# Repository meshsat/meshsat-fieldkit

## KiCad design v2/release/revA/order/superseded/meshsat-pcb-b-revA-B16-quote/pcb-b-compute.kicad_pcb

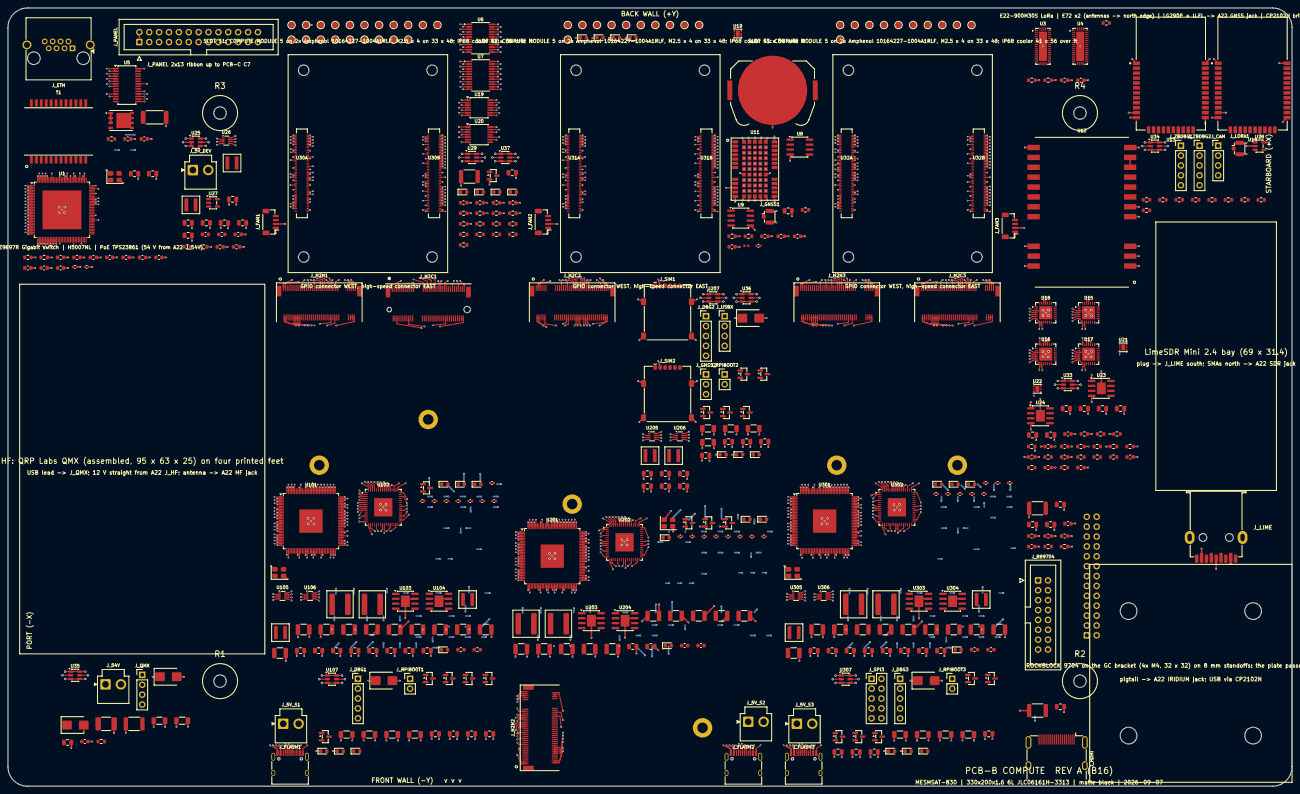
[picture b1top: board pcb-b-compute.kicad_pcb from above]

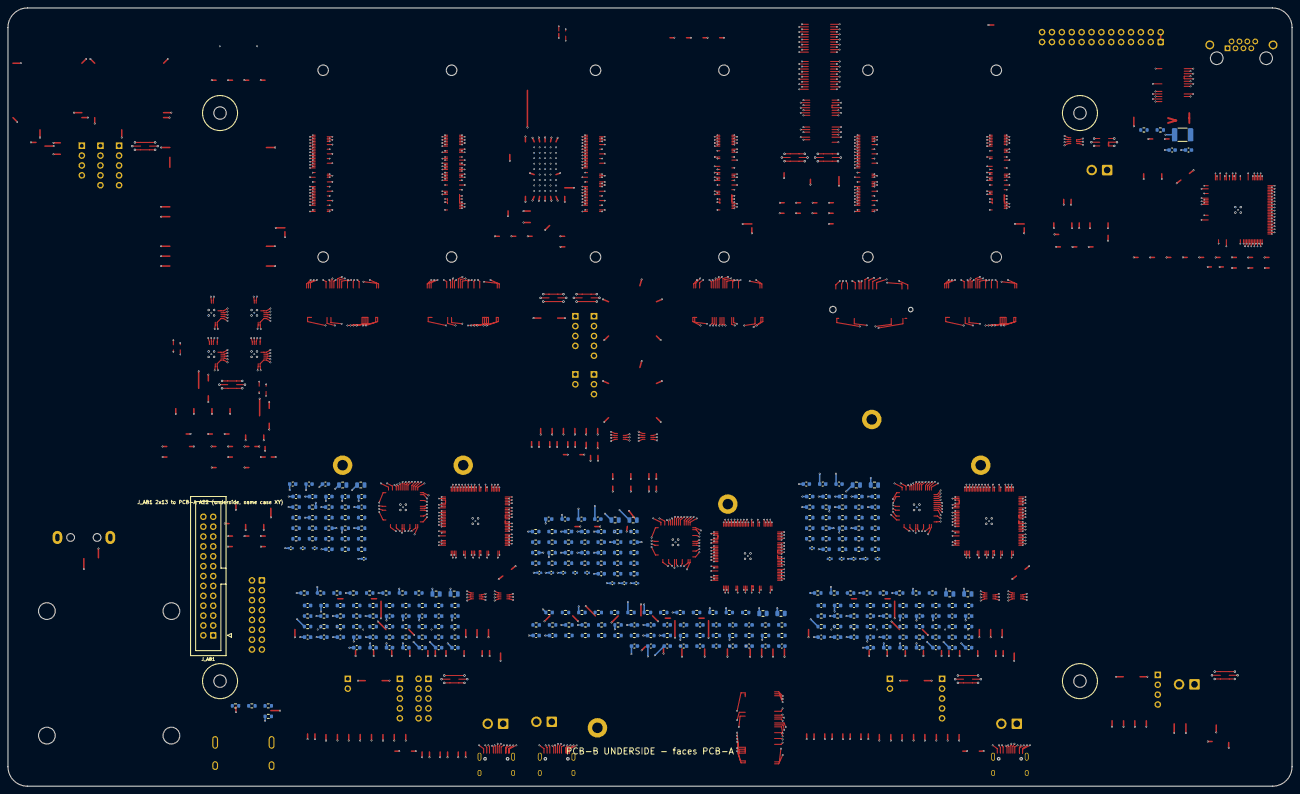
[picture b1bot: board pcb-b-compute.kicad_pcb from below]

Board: 6 copper layers, 330.0 x 200.0 mm, 777 parts (303 on the bottom side), 682 nets.

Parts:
BT1: CR2032 holder Keystone 3034: VBAT for the three m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; BatteryHolder_Keystone_3034_1x20mm
C1, C2, C101, C102, C103, C104, C201, C202, C203, C204, C301, C302, C303, C304: 100u 10V; C_1206_3216Metric
C3, C10, C17, C18, C19, C20, C21, C22, C23, C24, C25, C26, C29, C30, C31, C32, C36, C37, C38, C40, C44, C47, C49, C51, C54, C55, C57, C60, C62, C65, C66, C67, C68, C69, C70, C71, C110, C111, C118, C128, C133, C135, C136, C137, C138, C139, C140, C141, C142, C143, C144, C145, C146, C150, C158, C166, C167, C168, C169, C170, C171, C172, C173, C210, C211, C218, C228, C233, C235, C236, C237, C238, C239, C240, C241, C242, C243, C244, C245, C246, C250, C258, C266, C267, C268, C269, C270, C271, C272, C273, C286, C289, C310, C311, C318, C328, C333, C335, C336, C337, C338, C339, C340, C341, C342, C343, C344, C345, C346, C350, C358, C366, C367, C368, C369, C370, C371, C372, C373: 100n; C_0603_1608Metric
C4, C7, C16, C27, C28, C39, C41, C46, C53, C64, C105, C106, C107, C108, C109, C125, C130, C147, C148, C174, C205, C206, C207, C208, C209, C225, C230, C247, C248, C274, C305, C306, C307, C308, C309, C325, C330, C347, C348, C374: 10u; C_0805_2012Metric
C5, C6, C8, C9, C58, C63, C126, C127, C131, C132, C149, C157, C226, C227, C231, C232, C249, C257, C326, C327, C331, C332, C349, C357: 22u 6.3V; C_0805_2012Metric
C11, C56, C61, C129, C134, C229, C234, C329, C334: 10n; C_0603_1608Metric
C12, C13, C163, C263, C363: 1u; C_0603_1608Metric
C14, C15, C164, C165, C264, C265, C364, C365: 18p; C_0402_1005Metric
C33: 1n 2kV; C_1812_4532Metric
C34: 100n 100V; C_0805_2012Metric
C35: 10u 100V; C_1812_4532Metric
C42: 47p; C_0402_1005Metric
C43, C48, C50, C59: 4.7u; C_0805_2012Metric
C45, C52: 1n; C_0603_1608Metric
C112, C113, C114, C115, C116, C119, C120, C121, C122, C123, C212, C213, C214, C215, C216, C219, C220, C221, C222, C223, C312, C313, C314, C315, C316, C319, C320, C321, C322, C323: 22u 10V X7R 1210; C_1210_3225Metric
C117, C124, C217, C224, C317, C324: 3.3n; C_0603_1608Metric
C159, C160, C161, C162, C175, C176, C177, C178, C179, C180, C181, C182, C259, C260, C275, C276, C277, C278, C279, C280, C281, C282, C359, C360, C375, C376, C377, C378, C379, C380, C381, C382: 100n; C_0402_1005Metric
C287, C288, C290, C291: 33p; C_0402_1005Metric
D1, D101, D201, D301: SMBJ5.0A; D_SMB
D2: SMBJ58A; D_SMB
F1: 2A hold 1812; Fuse_1812_4532Metric
F2, F3, F4: 0.5A hold 1812; Fuse_1812_4532Metric
H1: M3 rod R1; MountingHole_3.2mm_M3
H2: M3 rod R2; MountingHole_3.2mm_M3
H3: M3 rod R3; MountingHole_3.2mm_M3
H4: M3 rod R4; MountingHole_3.2mm_M3
H5, H6, H7, H8: M2.5 standoff 4.0 mm, CM5 slot S1; MountingHole_2.7mm_M2.5
H9, H10, H11, H12: M2.5 standoff 4.0 mm, CM5 slot S2; MountingHole_2.7mm_M2.5
H13, H14, H15, H16: M2.5 standoff 4.0 mm, CM5 slot S3; MountingHole_2.7mm_M2.5
H17, H18, H19, H20: M4, GC 9704 bracket; MountingHole_4.3mm_M4
J_5V_DEV: USB device rail from A22 J_5V_DEV (JST-VH): + -; JST_VH_B2P-VH_1x02_P3.96mm_Vertical
J_5V_S1: 5 V slot rail S1 from A22 J_5V_S1 (JST-VH, 16 AWG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; JST_VH_B2P-VH_1x02_P3.96mm_Vertical
J_5V_S2: 5 V slot rail S2 from A22 J_5V_S2 (JST-VH, 16 AWG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; JST_VH_B2P-VH_1x02_P3.96mm_Vertical
J_5V_S3: 5 V slot rail S3 from A22 J_5V_S3 (JST-VH, 16 AWG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; JST_VH_B2P-VH_1x02_P3.96mm_Vertical
J_54V: 54 V PoE feed from A22 J_54V (JST-VH): + -; JST_VH_B2P-VH_1x02_P3.96mm_Vertical
J_AB1: A-B interconnect (IDC 2x13, underside, mates A22'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; IDC-Header_2x13_P2.54mm_Vertical
J_CAM: camera lead (USB 2.0, S1 hub port 3): 5V D- D+ GND; PinHeader_1x04_P2.54mm_Vertical
J_DBG1: console UART0 and the module I2C of S1 (3.3 V, be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; PinHeader_1x05_P2.54mm_Vertical
J_DBG2: console UART0 and the module I2C of S2 (3.3 V, be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; PinHeader_1x05_P2.54mm_Vertical
J_DBG3: console UART0 and the module I2C of S3 (3.3 V, be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; PinHeader_1x05_P2.54mm_Vertical
J_ETH: RJ45 jack (Amphenol RJHSE5380): patch lead to the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; RJ45_Amphenol_RJHSE5380
J_FAN1: IP68 cooler fan of S1 (JST-SH 1.0): 5V GND TACHO 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; JST_SH_BM04B-SRSS-TB_1x04-1MP_P1.00mm_Vertical
J_FAN2: IP68 cooler fan of S2 (JST-SH 1.0): 5V GND TACHO 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; JST_SH_BM04B-SRSS-TB_1x04-1MP_P1.00mm_Vertical
J_FAN3: IP68 cooler fan of S3 (JST-SH 1.0): 5V GND TACHO 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; JST_SH_BM04B-SRSS-TB_1x04-1MP_P1.00mm_Vertical
J_FLASH1, J_FLASH2, J_FLASH3: USB-C 2.0 receptacle; USB_C_Receptacle_HRO_TYPE-C-31-M-12
J_GNSS1: U.FL: pigtail to A22's GNSS jack J_RF4; U.FL_Hirose_U.FL-R-SMT-1_Vertical
J_GNSS2: LG290P UART2 (bench): GND TX RX; PinHeader_1x03_P2.54mm_Vertical
J_HDMI: HDMI type A receptacle (Molex 208658-1001): cable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; HDMI_A_Molex_208658-1001_Horizontal
J_LIME: USB 3.0 type A receptacle (Wuerth 692122030100 la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; USB3_A_Receptacle_Wuerth_692122030100
J_LORA1: U.FL: pigtail to A22's LoRa jack J_RF11; U.FL_Hirose_U.FL-R-SMT-1_Vertical
J_M2C1: M.2 E-key 2230 socket, TE 2199230-4, M2.5 standof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; M2_E-Key_Socket_2230
J_M2C2: M.2 B-key 3052 socket, TE 1-2199119-5, M2.5 stand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; M2_B-Key_Socket_3052
J_M2C3, J_M2N1, J_M2N2, J_M2N3: M.2 M-key 2242 socket, Amphenol MDT420M02001, M2.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; M2_M-Key_Socket_2242
J_PANEL: panel ribbon to PCB-C C7 (IDC 2x13): the RP2040 p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; IDC-Header_2x13_P2.54mm_Vertical
J_QMX: QMX USB lead (S2 hub port 4): VBUS D- D+ GND; pig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; PinHeader_1x04_P2.54mm_Vertical
J_RB9704: RockBLOCK 9704 16-pin (IDC 2x8) on the Ground Con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; IDC-Header_2x08_P2.54mm_Vertical
J_RPIBOOT1: nRPIBOOT jumper S1: fit to flash the eMMC over J_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; PinHeader_1x02_P2.54mm_Vertical
J_RPIBOOT2: nRPIBOOT jumper S2: fit to flash the eMMC over J_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; PinHeader_1x02_P2.54mm_Vertical
J_RPIBOOT3: nRPIBOOT jumper S3: fit to flash the eMMC over J_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; PinHeader_1x02_P2.54mm_Vertical
J_SIM1: nano-SIM push-push GCT SIM8060 (SIM 1); nanoSIM_GCT_SIM8060-6-0-14-00
J_SIM2: nano-SIM push-push GCT SIM8060 (SIM 2); nanoSIM_GCT_SIM8060-6-0-14-00
J_SPI3: SPI0 breakout of S3 (2x5): 3V3 GND MISO MOSI SCLK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; PinHeader_2x05_P2.54mm_Vertical
J_USBX: spare USB 2.0 header (S3 hub port 4): 5V D- D+ GND; PinHeader_1x04_P2.54mm_Vertical
J_ZBDBG1: CC2652P cJTAG ZBA (bench): 3V3 GND TMSC TCKC RESET; PinHeader_1x05_P2.54mm_Vertical
J_ZBDBG2: CC2652P cJTAG ZBB (bench): 3V3 GND TMSC TCKC RESET; PinHeader_1x05_P2.54mm_Vertical
L1: 4.7uH XAL4020-472ME; L_Coilcraft_XAL4020-XXX
L2, L103, L104, L203, L204, L303, L304: 2.2uH XAL4020-222ME; L_Coilcraft_XAL4020-XXX
L3: 27nH 0402 (antenna bias tee); L_0402_1005Metric
L101, L102, L201, L202, L301, L302: 3.3uH XAL6060-332ME; L_Coilcraft_XAL6060-XXX
LED1: green Ethernet port 1 link; LED_0603_1608Metric
LED2: green Ethernet port 2 link; LED_0603_1608Metric
LED3: green Ethernet port 3 link; LED_0603_1608Metric
LED4: green Ethernet port 4 link; LED_0603_1608Metric
LED6: red ZBA (DIO_7); LED_0603_1608Metric
LED7: green ZBA (DIO_8); LED_0603_1608Metric
LED8: red ZBB (DIO_7); LED_0603_1608Metric
LED9: green ZBB (DIO_8); LED_0603_1608Metric
LED11: green 5 V S1; LED_0603_1608Metric
LED12, LED22, LED32: green NVMe link (PORTSTATUS0); LED_0603_1608Metric
LED13, LED23, LED33: green card link (PORTSTATUS1); LED_0603_1608Metric
LED14, LED24, LED34: amber NVMe activity; LED_0603_1608Metric
LED15: blue WiFi link; LED_0603_1608Metric
LED16, LED26, LED36: green ACT (LED_nACT sinks); LED_0603_1608Metric
LED17, LED27, LED37: red PWR; LED_0603_1608Metric
LED21: green 5 V S2; LED_0603_1608Metric
LED25: amber 5G network; LED_0603_1608Metric
LED31: green 5 V S3; LED_0603_1608Metric
LED35: amber spare drive activity; LED_0603_1608Metric
Q1: FDMC3612 100 V N-FET, PoE port switch (PowerPAK S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; PowerPAK_SO-8_Single
Q2: 2N7002 expander -> switch reset; SOT-23
Q101, Q201, Q301: BC857: LED_nPWR must be buffered (datasheet Table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; SOT-23
Q102, Q103, Q104, Q105, Q202, Q203, Q204, Q205, Q302, Q303, Q304, Q305: 2N7002; SOT-23
Q106, Q206: 2N7002 EMCON -> W_DISABLE1#; SOT-23
Q207: 2N7002 expander -> FULL_CARD_POWER_OFF#; SOT-23
Q208: 2N7002 expander -> RESET#; SOT-23
R1, R103, R108, R113, R115, R144, R203, R208, R213, R215, R244, R303, R308, R313, R315, R344: 10k 1%; R_0603_1608Metric
R2: 20.0k 1%; R_0603_1608Metric
R3: 6.04k 1% (ISET); R_0603_1608Metric
R4, R11, R14, R21, R22, R25, R28, R29, R30, R31, R37, R41, R42, R44, R47, R56, R132, R133, R134, R135, R137, R138, R141, R145, R146, R149, R151, R154, R155, R156, R157, R158, R232, R233, R234, R235, R237, R238, R240, R241, R245, R246, R249, R251, R254, R255, R256, R257, R258, R332, R333, R334, R335, R337, R341, R345, R346, R349, R351, R354, R355, R356, R357, R358: 10k; R_0603_1608Metric
R5, R6, R7, R8, R24, R26, R27, R32, R33, R34, R35, R40, R101, R129, R130, R131, R136, R139, R148, R150, R201, R229, R230, R231, R236, R239, R248, R250, R301, R329, R330, R331, R336, R339, R348, R350: 1k; R_0603_1608Metric
R9, R10: 75; R_0603_1608Metric
R12: 0.255R 1% 2512; R_2512_6332Metric
R13: 24.9 (POE_P tie); R_0603_1608Metric
R15, R16, R48, R49, R50, R51, R52, R53, R106, R111, R112, R206, R211, R212, R306, R311, R312: 100k; R_0603_1608Metric
R17, R18, R54, R55: 2.2k; R_0603_1608Metric
R19: 15k; R_0603_1608Metric
R20, R105, R110, R205, R210, R305, R310: 22k; R_0603_1608Metric
R23: 10R; R_0603_1608Metric
R36, R43: 3.0 A (ILM); R_0603_1608Metric
R38, R45: 100k 1%; R_0603_1608Metric
R39, R46: 10k 1% (OVLO); R_0603_1608Metric
R57: 1k (strap [LED4_1, LED3_1] = 01: I2C management, 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; R_0603_1608Metric
R102, R107, R202, R207, R302, R307: 31.6k 1%; R_0603_1608Metric
R104, R109, R204, R209, R304, R309: 68k (RT: 500 kHz); R_0603_1608Metric
R114, R214, R314: 40.2k 1%; R_0603_1608Metric
R116, R216, R316: 26.7k 1%; R_0603_1608Metric
R117, R217, R317: 475 1% (IREF); R_0603_1608Metric
R118, R218, R318: 1.43k 1% (REXT); R_0603_1608Metric
R119, R120, R121, R123, R125, R126, R152, R153, R219, R220, R221, R223, R225, R226, R252, R253, R319, R320, R321, R323, R325, R326, R352, R353: 5.1k; R_0603_1608Metric
R122, R124, R128, R222, R224, R228, R322, R324, R328: 330; R_0603_1608Metric
R127, R227, R327: 4.7k; R_0603_1608Metric
R142, R242, R342: 9.53k 1%; R_0603_1608Metric
R143, R243, R343: 90.9k 1%; R_0603_1608Metric
R147, R247, R347: 1M; R_0603_1608Metric
S_LIME1, S_LIME2: tie slot; Slot_5x1.8_NPTH
S_QMX1, S_QMX2, S_QMX3, S_QMX4: tie slot; Slot_5x1.8_NPTH
T1: Pulse H5007NL 1000BASE-T magnetics (switch port 4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; Pulse_H5007NL
TP1: AB_SPARE; TestPoint_Pad_D1.5mm
TP2: +5V_DEV; TestPoint_Pad_D1.5mm
TP3: +3V3_DEV; TestPoint_Pad_D1.5mm
TP4: +1V2_KSZ; TestPoint_Pad_D1.5mm
TP5: +2V5_KSZ; TestPoint_Pad_D1.5mm
TP6: VBAT; TestPoint_Pad_D1.5mm
TP7: EMCON_HW; TestPoint_Pad_D1.5mm
TP8: ZEROIZE_HW; TestPoint_Pad_D1.5mm
TP9: GNSS_PPS; TestPoint_Pad_D1.5mm
TP10: SDA; TestPoint_Pad_D1.5mm
TP11: SCL; TestPoint_Pad_D1.5mm
TP12: +54V_POE; TestPoint_Pad_D1.5mm
TP13: POE_DRAIN; TestPoint_Pad_D1.5mm
TP14: +5V_LIME; TestPoint_Pad_D1.5mm
TP15: +5V_RB; TestPoint_Pad_D1.5mm
TP16: +5V_LORA; TestPoint_Pad_D1.5mm
TP17: +3V3_ZB; TestPoint_Pad_D1.5mm
TP18: HDMI_SEL1; TestPoint_Pad_D1.5mm
TP19: HDMI_SEL2; TestPoint_Pad_D1.5mm
TP20: +3V3_S1A; TestPoint_Pad_D1.5mm
TP21: +3V3_S1B; TestPoint_Pad_D1.5mm
TP22: +1V0_S1; TestPoint_Pad_D1.5mm
TP23: +1V1_S1; TestPoint_Pad_D1.5mm
TP24: +3V3_S2A; TestPoint_Pad_D1.5mm
TP25: +3V3_S2B; TestPoint_Pad_D1.5mm
TP26: +1V0_S2; TestPoint_Pad_D1.5mm
TP27: +1V1_S2; TestPoint_Pad_D1.5mm
TP28: +3V3_S3A; TestPoint_Pad_D1.5mm
TP29: +3V3_S3B; TestPoint_Pad_D1.5mm
TP30: +1V0_S3; TestPoint_Pad_D1.5mm
TP31: +1V1_S3; TestPoint_Pad_D1.5mm
TP41: EXP_SPARE1; TestPoint_Pad_D1.5mm
TP42: EXP_SPARE2; TestPoint_Pad_D1.5mm
TP43: EXP_SPARE3; TestPoint_Pad_D1.5mm
TP44: EXP_SPARE4; TestPoint_Pad_D1.5mm
TP45: EXP_SPARE5; TestPoint_Pad_D1.5mm
TP46: EXP_SPARE6; TestPoint_Pad_D1.5mm
TP47: EXP_SPARE7; TestPoint_Pad_D1.5mm
TP48: EXP_SPARE8; TestPoint_Pad_D1.5mm
TP49: EXP_SPARE9; TestPoint_Pad_D1.5mm
TP50: EXP_SPARE10; TestPoint_Pad_D1.5mm
TP51: EXP_SPARE11; TestPoint_Pad_D1.5mm
U1: Microchip KSZ9897RTXI seven-port Gigabit switch: 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; TQFP-128_14x14mm_P0.4mm_EP10.0
U3: TI TS3DV642A0RUAR HDMI 2:1 switch (HDMI1 / HDMI2 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; WQFN-42-1EP_3.5x9mm_P0.5mm_EP2.05x7.55mm
U4: TI TS3DV642A0RUAR HDMI 2:1 switch (HDMIM / HDMI3 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; WQFN-42-1EP_3.5x9mm_P0.5mm_EP2.05x7.55mm
U5: TI TPS23861PWR PoE PSE controller, port 1 to the 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; TSSOP-28_4.4x9.7mm_P0.65mm
U6: PCA9555PW 0x20: outputs (switch reset, rail enabl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; TSSOP-24_4.4x7.8mm_P0.65mm
U7: PCA9555PW 0x25: inputs (faults, RockBLOCK status)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; TSSOP-24_4.4x7.8mm_P0.65mm
U8: ATECC608B-SSHDA-T secure element (I2C 0x60): keys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; SOIC-8_3.9x4.9mm_P1.27mm
U9: DS3231MZ+ holdover clock (I2C 0x68), CR2032 backed; SOIC-8_3.9x4.9mm_P1.27mm
U10: TMP117AIDRVR board temperature under the coolers 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; WSON-6-1EP_2x2mm_P0.65mm_EP1x1.6mm
U11: Quectel LG290P03AAMD GNSS RTK module: UART1 to th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; Quectel_LG290P
U12: Ebyte E22-900M30S 1 W LoRa (SX1262) on S3 SPI0 CE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; Ebyte_E22-900M30S
U13: Ebyte E72-2G4M20S1E CC2652P (Zigbee coordinator):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; Ebyte_E72-2G4M20S1E
U14: Ebyte E72-2G4M20S1E CC2652P (OpenThread RCP for M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; Ebyte_E72-2G4M20S1E
U15: CP2102N-A02-GQFN28 USB-UART bridge (GNSS); QFN-28-1EP_5x5mm_P0.5mm_EP3.35x3.35mm
U16: CP2102N-A02-GQFN28 USB-UART bridge (ZBA); QFN-28-1EP_5x5mm_P0.5mm_EP3.35x3.35mm
U17: CP2102N-A02-GQFN28 USB-UART bridge (ZBB); QFN-28-1EP_5x5mm_P0.5mm_EP3.35x3.35mm
U18: CP2102N-A02-GQFN28 USB-UART bridge (RB); QFN-28-1EP_5x5mm_P0.5mm_EP3.35x3.35mm
U19: 74LVC08APW quad AND: LimeSDR (hub port power AND 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; TSSOP-14_4.4x5mm_P0.65mm
U20: 74LVC08APW quad AND: E72 radios (EMCON AND softwa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; TSSOP-14_4.4x5mm_P0.65mm
U21, U22: TPS22810DRV; WSON-6-1EP_2x2mm_P0.65mm_EP1x1.6mm
U23: TPS259631DDAR eFuse +5V_DEV -> +5V_LIME (3.0 A (I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; SOIC-8-1EP_3.9x4.9mm_P1.27mm_EP2.29x3mm
U24: TPS259631DDAR eFuse +5V_DEV -> +5V_RB (3.0 A (ILM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; SOIC-8-1EP_3.9x4.9mm_P1.27mm_EP2.29x3mm
U25: AP63203WU-7 3.3 V 2 A buck: the shared logic (+3V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; TSOT-23-6
U26: TPS62933DRLR buck 1.2 V Ethernet switch core; SOT-583-8
U27: AP2112K-2.5 LDO: the switch's 2.5 V analog rail; SOT-23-5
U28: TPS2065CDBV; SOT-23-5
U29, U33, U34, U35, U36, U37, U107, U207, U307: USBLC6-2SC6; SOT-23-6
U30A: Amphenol 10164227-1004A1RLF receptacle A, slot S1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; CM5_Conn_A_10164227
U30B: Amphenol 10164227-1004A1RLF receptacle B, slot S1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; CM5_Conn_B_10164227
U31A: Amphenol 10164227-1004A1RLF receptacle A, slot S2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; CM5_Conn_A_10164227
U31B: Amphenol 10164227-1004A1RLF receptacle B, slot S2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; CM5_Conn_B_10164227
U32A: Amphenol 10164227-1004A1RLF receptacle A, slot S3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; CM5_Conn_A_10164227
U32B: Amphenol 10164227-1004A1RLF receptacle B, slot S3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; CM5_Conn_B_10164227
U101: Diodes PI7C9X2G404SL PCIe 2.0 switch, slot S1: up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; LQFP-128_14x14mm_P0.4mm_EP6.0
U102: TI TUSB8041IRGCR four-port USB 3.0 hub, slot S1 (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; QFN-64-1EP_9x9mm_P0.5mm_EP4.7x4.7mm
U103: AP64500SP-13 5 A buck, 3.3 V rail +3V3_S1A; SOIC-8-1EP_3.9x4.9mm_P1.27mm_EP2.29x3mm
U104: AP64500SP-13 5 A buck, 3.3 V rail +3V3_S1B; SOIC-8-1EP_3.9x4.9mm_P1.27mm_EP2.29x3mm
U105: TPS62933DRLR buck 1.0 V PCIe switch core S1; SOT-583-8
U106: TPS62933DRLR buck 1.1 V hub core S1; SOT-583-8
U201: Diodes PI7C9X2G404SL PCIe 2.0 switch, slot S2: up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; LQFP-128_14x14mm_P0.4mm_EP6.0
U202: TI TUSB8041IRGCR four-port USB 3.0 hub, slot S2 (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; QFN-64-1EP_9x9mm_P0.5mm_EP4.7x4.7mm
U203: AP64500SP-13 5 A buck, 3.3 V rail +3V3_S2A; SOIC-8-1EP_3.9x4.9mm_P1.27mm_EP2.29x3mm
U204: AP64500SP-13 5 A buck, 3.3 V rail +3V3_S2B; SOIC-8-1EP_3.9x4.9mm_P1.27mm_EP2.29x3mm
U205: TPS62933DRLR buck 1.0 V PCIe switch core S2; SOT-583-8
U206: TPS62933DRLR buck 1.1 V hub core S2; SOT-583-8
U301: Diodes PI7C9X2G404SL PCIe 2.0 switch, slot S3: up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; LQFP-128_14x14mm_P0.4mm_EP6.0
U302: TI TUSB8041IRGCR four-port USB 3.0 hub, slot S3 (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; QFN-64-1EP_9x9mm_P0.5mm_EP4.7x4.7mm
U303: AP64500SP-13 5 A buck, 3.3 V rail +3V3_S3A; SOIC-8-1EP_3.9x4.9mm_P1.27mm_EP2.29x3mm
U304: AP64500SP-13 5 A buck, 3.3 V rail +3V3_S3B; SOIC-8-1EP_3.9x4.9mm_P1.27mm_EP2.29x3mm
U305: TPS62933DRLR buck 1.0 V PCIe switch core S3; SOT-583-8
U306: TPS62933DRLR buck 1.1 V hub core S3; SOT-583-8
Y1: 25 MHz 3225; Crystal_SMD_3225-4Pin_3.2x2.5mm
Y101, Y201, Y301: 24 MHz 3225; Crystal_SMD_3225-4Pin_3.2x2.5mm

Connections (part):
/5G_OFF: Q207.1, U6.10
/5G_PWROFF_n: J_M2C2.6, Q207.3, R238.1
/5G_RESET: Q208.1, U6.11
/5G_RST_n: J_M2C2.67, Q208.3, R240.1
/5G_W_DIS_n: J_M2C2.8, Q206.2, R237.1
/5G_nLED: J_M2C2.10, LED25.1
/+1V0_S1: C126.1, C127.1, C141.1, C142.1, C143.1, C144.1, C145.1, C146.1, C148.1, L103.2, R113.1, TP22.1, U101.3, U101.13, U101.14, U101.23, U101.29, U101.31, U101.40, U101.55, U101.62, U101.65, U101.91, U101.99, U101.105, U101.108, U101.119, U101.125
/+1V0_S2: C226.1, C227.1, C241.1, C242.1, C243.1, C244.1, C245.1, C246.1, C248.1, L203.2, R213.1, TP26.1, U201.3, U201.13, U201.14, U201.23, U201.29, U201.31, U201.40, U201.55, U201.62, U201.65, U201.91, U201.99, U201.105, U201.108, U201.119, U201.125
/+1V0_S3: C326.1, C327.1, C341.1, C342.1, C343.1, C344.1, C345.1, C346.1, C348.1, L303.2, R313.1, TP30.1, U301.3, U301.13, U301.14, U301.23, U301.29, U301.31, U301.40, U301.55, U301.62, U301.65, U301.91, U301.99, U301.105, U301.108, U301.119, U301.125
/+1V1_S1: C131.1, C132.1, C166.1, C167.1, C168.1, C169.1, C174.1, L104.2, R115.1, TP23.1, U102.5, U102.8, U102.13, U102.21, U102.28, U102.31, U102.51, U102.57
/+1V1_S2: C231.1, C232.1, C266.1, C267.1, C268.1, C269.1, C274.1, L204.2, R215.1, TP27.1, U202.5, U202.8, U202.13, U202.21, U202.28, U202.31, U202.51, U202.57
/+1V1_S3: C331.1, C332.1, C366.1, C367.1, C368.1, C369.1, C374.1, L304.2, R315.1, TP31.1, U302.5, U302.8, U302.13, U302.21, U302.28, U302.31, U302.51, U302.57
/+1V2_KSZ: C8.1, C9.1, C18.1, C21.1, C24.1, C27.1, L2.2, R1.1, TP4.1, U1.3, U1.11, U1.14, U1.19, U1.23, U1.30, U1.36, U1.41, U1.45, U1.56, U1.74, U1.87, U1.104, U1.110, U1.114, U1.119, U1.124
/+1V8_CM1: U30A.88, U30A.90
/+1V8_CM2: U31A.88, U31A.90
/+1V8_CM3: U32A.88, U32A.90
/+2V5_KSZ: C12.1, C19.1, C22.1, C25.1, C28.1, TP5.1, U1.10, U1.22, U1.33, U1.44, U1.111, U1.122, U1.128, U27.5
/+3V3_CM1: C109.1, C110.1, Q101.2, Q102.1, Q103.1, Q104.1, Q105.1, R111.1, R148.1, R151.2, R154.2, R155.2, R156.2, R157.2, U30A.78, U30A.84, U30A.86
/+3V3_CM2: C209.1, C210.1, Q201.2, Q202.1, Q203.1, Q204.1, Q205.1, R211.1, R248.1, R251.2, R254.2, R255.2, R256.2, R257.2, U31A.78, U31A.84, U31A.86
/+3V3_CM3: C309.1, C310.1, Q301.2, Q302.1, Q303.1, Q304.1, Q305.1, R311.1, R348.1, R351.2, R354.2, R355.2, R356.2, R357.2, U32A.78, U32A.84, U32A.86
/+3V3_DEV: C5.1, C6.1, C13.1, C17.1, C20.1, C23.1, C26.1, C36.1, C37.1, C38.1, C40.1, C41.1, C65.1, C66.1, C67.1, C68.1, C69.1, C70.1, C71.1, L1.2, R4.2, R5.1, R6.1, R7.1, R8.1, R11.2, R14.2, R21.2, R37.2, R41.2, R42.2, R44.2, R47.2, R54.2, R55.2, R56.2, R158.2, R258.2, R358.2, TP3.1, U1.61, U1.77, U1.99, U3.1, U4.1, U5.1, U6.24, U7.3, U7.21, U7.24, U8.8, U9.2, U10.4, U10.5, U11.23, U19.14, U20.14, U22.6, U25.1, U27.1, U27.3, U29.5, U37.5
/+3V3_S1A: C114.1, C115.1, C116.1, C157.1, C158.1, J_M2C1.2, J_M2C1.4, J_M2C1.72, J_M2C1.74, L101.2, Q106.1, R102.1, R134.2, R137.2, R138.2, R139.1, TP20.1
/+3V3_S1B: C121.1, C122.1, C123.1, C135.1, C136.1, C137.1, C138.1, C139.1, C140.1, C147.1, C149.1, C150.1, C170.1, C171.1, C172.1, C173.1, J_M2N1.2, J_M2N1.4, J_M2N1.12, J_M2N1.14, J_M2N1.16, J_M2N1.18, J_M2N1.70, J_M2N1.72, J_M2N1.74, L102.2, R107.1, R119.2, R120.2, R121.2, R123.2, R125.2, R126.2, R130.1, R131.1, R132.2, R133.2, R136.1, R141.2, R145.2, R146.2, TP21.1, U101.1, U101.8, U101.15, U101.49, U101.64, U101.79, U101.82, U101.84, U101.96, U101.113, U102.16, U102.34, U102.52, U102.63
/+3V3_S2A: C214.1, C215.1, C216.1, C257.1, C258.1, J_M2C2.2, J_M2C2.4, J_M2C2.70, J_M2C2.72, J_M2C2.74, L201.2, Q206.1, R202.1, R234.2, R237.2, R238.2, R239.1, R240.2, TP24.1
/+3V3_S2B: C221.1, C222.1, C223.1, C235.1, C236.1, C237.1, C238.1, C239.1, C240.1, C247.1, C249.1, C250.1, C270.1, C271.1, C272.1, C273.1, J_M2N2.2, J_M2N2.4, J_M2N2.12, J_M2N2.14, J_M2N2.16, J_M2N2.18, J_M2N2.70, J_M2N2.72, J_M2N2.74, L202.2, R207.1, R219.2, R220.2, R221.2, R223.2, R225.2, R226.2, R230.1, R231.1, R232.2, R233.2, R236.1, R241.2, R245.2, R246.2, TP25.1, U201.1, U201.8, U201.15, U201.49, U201.64, U201.79, U201.82, U201.84, U201.96, U201.113, U202.16, U202.34, U202.52, U202.63
/+3V3_S3A: C314.1, C315.1, C316.1, C357.1, C358.1, J_M2C3.2, J_M2C3.4, J_M2C3.12, J_M2C3.14, J_M2C3.16, J_M2C3.18, J_M2C3.70, J_M2C3.72, J_M2C3.74, L301.2, R302.1, R334.2, R339.1, TP28.1
/+3V3_S3B: C321.1, C322.1, C323.1, C335.1, C336.1, C337.1, C338.1, C339.1, C340.1, C347.1, C349.1, C350.1, C370.1, C371.1, C372.1, C373.1, J_M2N3.2, J_M2N3.4, J_M2N3.12, J_M2N3.14, J_M2N3.16, J_M2N3.18, J_M2N3.70, J_M2N3.72, J_M2N3.74, J_SPI3.1, L302.2, R25.2, R307.1, R319.2, R320.2, R321.2, R323.2, R325.2, R326.2, R330.1, R331.1, R332.2, R333.2, R336.1, R341.2, R345.2, R346.2, TP29.1, U301.1, U301.8, U301.15, U301.49, U301.64, U301.79, U301.82, U301.84, U301.96, U301.113, U302.16, U302.34, U302.52, U302.63
/+3V3_ZB: C53.1, C54.1, C55.1, J_ZBDBG1.1, J_ZBDBG2.1, R28.2, R29.2, R30.2, R31.2, TP17.1, U13.20, U14.20, U22.1
/+5V_CAM: C64.1, J_CAM.1, U28.1, U34.5
/+5V_DEV: C1.1, C2.1, C4.1, C7.1, C57.1, C62.1, D1.1, F1.1, F2.1, F3.1, F4.1, J_5V_DEV.1, R38.1, R45.1, TP2.1, U21.6, U23.4, U24.4, U25.2, U25.3, U26.2, U26.3, U28.5
/+5V_HDMI: C39.1, F2.2, J_HDMI.18, R17.2, R18.2
/+5V_LIME: C58.1, J_LIME.1, TP14.1, U23.5, U33.5
/+5V_LORA: C46.1, C47.1, TP16.1, U12.9, U12.10, U21.1
/+5V_RB: C63.1, J_RB9704.15, TP15.1, U24.5
/+5V_S1: C101.1, C102.1, C103.1, C104.1, C105.1, C106.1, C107.1, C108.1, C112.1, C113.1, C119.1, C120.1, C125.1, C130.1, D101.1, J_5V_S1.1, J_FAN1.1, R101.1, R143.1, U18.7, U18.8, U30A.77, U30A.79, U30A.81, U30A.83, U30A.85, U30A.87, U103.2, U104.2, U105.3, U106.3
/+5V_S2: C201.1, C202.1, C203.1, C204.1, C205.1, C206.1, C207.1, C208.1, C212.1, C213.1, C219.1, C220.1, C225.1, C230.1, D201.1, J_5V_S2.1, J_FAN2.1, R201.1, R243.1, U15.7, U15.8, U16.7, U16.8, U17.7, U17.8, U31A.77, U31A.79, U31A.81, U31A.83, U31A.85, U31A.87, U203.2, U204.2, U205.3, U206.3
/+5V_S3: C301.1, C302.1, C303.1, C304.1, C305.1, C306.1, C307.1, C308.1, C312.1, C313.1, C319.1, C320.1, C325.1, C330.1, D301.1, J_5V_S3.1, J_FAN3.1, R301.1, R343.1, U32A.77, U32A.79, U32A.81, U32A.83, U32A.85, U32A.87, U303.2, U304.2, U305.3, U306.3
/+5V_USBX: F4.2, J_USBX.1, U36.5
/+54V_POE: C34.1, C35.1, D2.1, J_54V.1, R13.1, TP12.1, U5.28
/AB_SPARE: J_AB1.25, TP1.1
/BOB: C33.1, R9.2, R10.2
/BT_nDIS1: U6.16, U30A.91
/BT_nDIS2: U6.17, U31A.91
/BT_nDIS3: U6.18, U32A.91
/CAM_DM: J_CAM.2, U34.3, U34.4, U102.18
/CAM_DP: J_CAM.3, U34.1, U34.6, U102.17
/CAM_EN: R48.1, U6.9, U28.4
/CAM_FLT: R47.1, U7.6, U28.3
/CARD1_CLKREQ_n: J_M2C1.53, R134.1
/CARD1_CLK_N: J_M2C1.49, U101.77
/CARD1_CLK_P: J_M2C1.47, U101.78
/CARD1_RX_N: J_M2C1.43, U101.107
/CARD1_RX_P: J_M2C1.41, U101.106
/CARD1_TX_N: J_M2C1.37, U101.103
/CARD1_TX_P: J_M2C1.35, U101.102
/CARD2_CLKREQ_n: J_M2C2.52, R234.1
/CARD2_CLK_N: J_M2C2.53, U201.77
/CARD2_CLK_P: J_M2C2.55, U201.78
/CARD2_RX_N: J_M2C2.41, U201.107
/CARD2_RX_P: J_M2C2.43, U201.106
/CARD2_TX_N: J_M2C2.47, U201.103
/CARD2_TX_P: J_M2C2.49, U201.102
/CARD3_CLKREQ_n: J_M2C3.52, R334.1
/CARD3_CLK_N: J_M2C3.53, U301.77
/CARD3_CLK_P: J_M2C3.55, U301.78
/CARD3_DEVSLP: J_M2C3.38, R337.1
/CARD3_RX_N: J_M2C3.41, U301.107
/CARD3_RX_P: J_M2C3.43, U301.106
/CARD3_TX_N: J_M2C3.47, U301.103
/CARD3_TX_P: J_M2C3.49, U301.102
/CARD3_nLED: J_M2C3.10, LED35.1
/CC1_F1: J_FLASH1.A5, R152.1
/CC1_F2: J_FLASH2.A5, R252.1
/CC1_F3: J_FLASH3.A5, R352.1
/CC2_F1: J_FLASH1.B5, R153.1
/CC2_F2: J_FLASH2.B5, R253.1
/CC2_F3: J_FLASH3.B5, R353.1
/DEV_BST: C3.1, U25.6
/DEV_SW: C3.2, L1.1, U25.5
/E22_CT: C45.1, U21.3
/E22_EN: U19.11, U21.5
/E72_CT: C52.1, U22.3
/E72_EN: U20.3, U22.5
/EMCON_HW: J_AB1.17, J_PANEL.8, Q106.3, Q206.3, TP7.1, U19.1, U19.9, U19.12, U20.1
/EN33_S1: R111.2, R112.1, U104.3, U105.2, U106.2
/EN33_S2: R211.2, R212.1, U204.3, U205.2, U206.2
/EN33_S3: R311.2, R312.1, U304.3, U305.2, U306.2
/ETH1_P0_N: C176.1, U30A.10
/ETH1_P0_P: C175.1, U30A.12
/ETH1_P1_N: C178.1, U30A.6
/ETH1_P1_P: C177.1, U30A.4
/ETH1_P2_N: C180.1, U30A.9
/ETH1_P2_P: C179.1, U30A.11
/ETH1_P3_N: C182.1, U30A.5
/ETH1_P3_P: C181.1, U30A.3
/ETH2_P0_N: C276.1, U31A.10
/ETH2_P0_P: C275.1, U31A.12
/ETH2_P1_N: C278.1, U31A.6
/ETH2_P1_P: C277.1, U31A.4
/ETH2_P2_N: C280.1, U31A.9
/ETH2_P2_P: C279.1, U31A.11
/ETH2_P3_N: C282.1, U31A.5
/ETH2_P3_P: C281.1, U31A.3
/ETH3_P0_N: C376.1, U32A.10
/ETH3_P0_P: C375.1, U32A.12
/ETH3_P1_N: C378.1, U32A.6
/ETH3_P1_P: C377.1, U32A.4
/ETH3_P2_N: C380.1, U32A.9
/ETH3_P2_P: C379.1, U32A.11
/ETH3_P3_N: C382.1, U32A.5
/ETH3_P3_P: C381.1, U32A.3
/EXP_INT: J_AB1.15, J_PANEL.6, R56.1, U1.94, U5.6, U6.1, U7.1, U9.3, U10.3
/EXP_SPARE1: TP41.1, U7.9
/EXP_SPARE2: TP42.1, U7.10
/EXP_SPARE3: TP43.1, U7.11
/EXP_SPARE4: TP44.1, U7.13
/EXP_SPARE5: TP45.1, U7.14
/EXP_SPARE6: TP46.1, U7.15
/EXP_SPARE7: TP47.1, U7.16
/EXP_SPARE8: TP48.1, U7.17
/EXP_SPARE9: TP49.1, U7.18
/EXP_SPARE10: TP50.1, U7.19
/EXP_SPARE11: TP51.1, U7.20
/FAN_PWM1: J_FAN1.4, R151.1, U30A.19
/FAN_PWM2: J_FAN2.4, R251.1, U31A.19
/FAN_PWM3: J_FAN3.4, R351.1, U32A.19
/FAN_TACHO1: J_FAN1.3, U30A.16
/FAN_TACHO2: J_FAN2.3, U31A.16
/FAN_TACHO3: J_FAN3.3, U32A.16
/GNSS_3V3: C43.1, C44.1, R24.2, U15.6
/GNSS_ANT: C42.1, J_GNSS1.1, L3.2
/GNSS_BIAS: L3.1, R23.2
/GNSS_DM: U15.5, U202.2
/GNSS_DP: U15.4, U202.1
/GNSS_PPS: Q104.3, Q204.3, Q304.3, R22.1, TP9.1, U11.3
/GNSS_PPS_CM1: Q104.2, R156.1, U30A.46
/GNSS_PPS_CM2: Q204.2, R256.1, U31A.46
/GNSS_PPS_CM3: Q304.2, R356.1, U32A.46
/GNSS_RF_IN: C42.2, U11.11
/GNSS_RST: R24.1, U15.9
/GNSS_RST_n: R21.1, U11.8
/GNSS_RXD: U11.21, U15.26
/GNSS_RXD2: J_GNSS2.3, U11.7
/GNSS_TXD: U11.20, U15.25
/GNSS_TXD2: J_GNSS2.2, U11.6
/GNSS_VDD_RF: R23.1, U11.9
/HB1: J_PANEL.18, Q105.3, R158.1
/HB2: J_PANEL.19, Q205.3, R258.1
/HB3: J_PANEL.20, Q305.3, R358.1
/HB_CM1: Q105.2, R157.1, U30A.29
/HB_CM2: Q205.2, R257.1, U31A.29
/HB_CM3: Q305.2, R357.1, U32A.29
/HDMI1_CEC: U3.18, U30B.151
/HDMI1_CK_N: U3.31, U30B.190
/HDMI1_CK_P: U3.32, U30B.188
/HDMI1_D0_N: U3.37, U30B.184
/HDMI1_D0_P: U3.38, U30B.182
/HDMI1_D1_N: U3.35, U30B.178
/HDMI1_D1_P: U3.36, U30B.176
/HDMI1_D2_N: U3.33, U30B.172
/HDMI1_D2_P: U3.34, U30B.170
/HDMI1_HPD: U3.19, U30B.153
/HDMI1_SCL: U3.42, U30B.200
/HDMI1_SDA: U3.41, U30B.199
/HDMI2_CEC: U3.20, U31B.151
/HDMI2_CK_N: U3.22, U31B.190
/HDMI2_CK_P: U3.23, U31B.188
/HDMI2_D0_N: U3.28, U31B.184
/HDMI2_D0_P: U3.29, U31B.182
/HDMI2_D1_N: U3.26, U31B.178
/HDMI2_D1_P: U3.27, U31B.176
/HDMI2_D2_N: U3.24, U31B.172
/HDMI2_D2_P: U3.25, U31B.170
/HDMI2_HPD: U3.21, U31B.153
/HDMI2_SCL: U3.40, U31B.200
/HDMI2_SDA: U3.39, U31B.199
/HDMI3_CEC: U4.20, U32B.151
/HDMI3_CK_N: U4.22, U32B.190
/HDMI3_CK_P: U4.23, U32B.188
/HDMI3_D0_N: U4.28, U32B.184
/HDMI3_D0_P: U4.29, U32B.182
/HDMI3_D1_N: U4.26, U32B.178
/HDMI3_D1_P: U4.27, U32B.176
/HDMI3_D2_N: U4.24, U32B.172
/HDMI3_D2_P: U4.25, U32B.170
/HDMI3_HPD: U4.21, U32B.153
/HDMI3_SCL: U4.40, U32B.200
/HDMI3_SDA: U4.39, U32B.199
/HDMIM_CEC: U3.15, U4.18
/HDMIM_CK_N: U3.13, U4.31
/HDMIM_CK_P: U3.12, U4.32
/HDMIM_D0_N: U3.6, U4.37
/HDMIM_D0_P: U3.5, U4.38
/HDMIM_D1_N: U3.8, U4.35
/HDMIM_D1_P: U3.7, U4.36
/HDMIM_D2_N: U3.11, U4.33
/HDMIM_D2_P: U3.10, U4.34
/HDMIM_HPD: U3.14, U4.19
/HDMIM_SCL: U3.3, U4.42
/HDMIM_SDA: U3.4, U4.41
/HDMIO_CEC: J_HDMI.13, U4.15
/HDMIO_CK_N: J_HDMI.12, U4.13
/HDMIO_CK_P: J_HDMI.10, U4.12
/HDMIO_D0_N: J_HDMI.9, U4.6
/HDMIO_D0_P: J_HDMI.7, U4.5
/HDMIO_D1_N: J_HDMI.6, U4.8
/HDMIO_D1_P: J_HDMI.4, U4.7
/HDMIO_D2_N: J_HDMI.3, U4.11
/HDMIO_D2_P: J_HDMI.1, U4.10
/HDMIO_HPD: R19.2, R20.1, U4.14
/HDMIO_HPD_IN: J_HDMI.19, R19.1
/HDMIO_SCL: J_HDMI.15, R17.1, U4.3
/HDMIO_SDA: J_HDMI.16, R18.1, U4.4
/HDMI_SEL1: J_PANEL.12, R15.1, TP18.1, U3.17
/HDMI_SEL2: J_PANEL.13, R16.1, TP19.1, U4.17
/HDMI_SW_EN: R14.1, U3.2, U3.16, U4.2, U4.16
/HUB1_D1TX_N: C162.1, U102.4
/HUB1_D1TX_P: C161.1, U102.3
/HUB1_PWRPOL: R146.1, U102.41
/HUB1_R1: R142.1, U102.64
/HUB1_RST_n: C163.1, R141.1, U102.50
/HUB1_SMBUS_n: R145.1, U102.39
/HUB1_SSTX_N: C160.1, U102.56
/HUB1_SSTX_P: C159.1, U102.55
/HUB1_VBUS: R143.2, R144.1, U102.48
/HUB1_XI: C164.1, R147.1, U102.62, Y101.1
/HUB1_XO: C165.1, R147.2, U102.61, Y101.3
/HUB2_PWRPOL: R246.1, U202.41
/HUB2_R1: R242.1, U202.64
/HUB2_RST_n: C263.1, R241.1, U202.50
/HUB2_SMBUS_n: R245.1, U202.39
/HUB2_SSTX_N: C260.1, U202.56
/HUB2_SSTX_P: C259.1, U202.55
/HUB2_VBUS: R243.2, R244.1, U202.48
/HUB2_XI: C264.1, R247.1, U202.62, Y201.1
/HUB2_XO: C265.1, R247.2, U202.61, Y201.3
/HUB3_PWRPOL: R346.1, U302.41
/HUB3_R1: R342.1, U302.64
/HUB3_RST_n: C363.1, R341.1, U302.50
/HUB3_SMBUS_n: R345.1, U302.39
/HUB3_SSTX_N: C360.1, U302.56
/HUB3_SSTX_P: C359.1, U302.55
/HUB3_VBUS: R343.2, R344.1, U302.48
/HUB3_XI: C364.1, R347.1, U302.62, Y301.1
/HUB3_XO: C365.1, R347.2, U302.61, Y301.3
/KSZC_BST: C10.1, U26.6
/KSZC_FB: R1.2, R2.1, U26.8
/KSZC_SS: C11.1, U26.7
/KSZC_SW: C10.2, L2.1, U26.5
/KSZ_ISET: R3.1, U1.127
/KSZ_LED1: LED1.1, U1.105
/KSZ_LED2: LED2.1, U1.91
/KSZ_LED3: LED3.1, U1.88
/KSZ_LED4: LED4.1, U1.85
/KSZ_RST: Q2.1, U6.4
/KSZ_RST_n: C16.1, Q2.3, R4.1, U1.96
/KSZ_STRAP_I2C: R57.1, U1.86
/KSZ_XI: C14.1, U1.126, Y1.1
/KSZ_XO: C15.1, U1.125, Y1.3
/LED_5G_A: LED25.2, R239.2
/LED_5V_A1: LED11.2, R101.2
/LED_5V_A2: LED21.2, R201.2
/LED_5V_A3: LED31.2, R301.2
/LED_ACT_A1: LED16.2, R148.2
/LED_ACT_A2: LED26.2, R248.2
/LED_ACT_A3: LED36.2, R348.2
/LED_C3_A: LED35.2, R339.2
/LED_KSZ_A1: LED1.2, R5.2
/LED_KSZ_A2: LED2.2, R6.2
/LED_KSZ_A3: LED3.2, R7.2
/LED_KSZ_A4: LED4.2, R8.2
/LED_NV_A1: LED14.2, R136.2
/LED_NV_A2: LED24.2, R236.2
/LED_NV_A3: LED34.2, R336.2
/LED_PST0_A1: LED12.2, R130.2
/LED_PST0_A2: LED22.2, R230.2
/LED_PST0_A3: LED32.2, R330.2
/LED_PST1_A1: LED13.2, R131.2
/LED_PST1_A2: LED23.2, R231.2
/LED_PST1_A3: LED33.2, R331.2
/LED_PWR_A1: LED17.2, R150.2
/LED_PWR_A2: LED27.2, R250.2
/LED_PWR_A3: LED37.2, R350.2
/LED_WIFI_A: LED15.2, R139.2
/LED_ZBAG_A: LED7.2, R34.2
/LED_ZBAR_A: LED6.2, R32.2
/LED_ZBBG_A: LED9.2, R35.2
/LED_ZBBR_A: LED8.2, R33.2
/LED_nACT1: LED16.1, U30A.21
/LED_nACT2: LED26.1, U31A.21
/LED_nACT3: LED36.1, U32A.21
/LED_nPWR1: R149.1, U30A.95
/LED_nPWR2: R249.1, U31A.95
/LED_nPWR3: R349.1, U32A.95
/LIME_DM: J_LIME.2, U33.3, U33.4, U102.2
/LIME_DP: J_LIME.3, U33.1, U33.6, U102.1
/LIME_EN: U19.6, U23.3
/LIME_EN_A: U19.3, U19.4
/LIME_FLT: R37.1, U7.4, U23.6, U102.46
/LIME_HW_EN: R49.1, U19.2, U102.36
/LIME_SSRX_N: C162.2, J_LIME.5
/LIME_SSRX_P: C161.2, J_LIME.6
/LIME_SSTX_N: J_LIME.8, U102.7
/LIME_SSTX_P: J_LIME.9, U102.6
/LIME_SW_EN: R50.1, U6.5, U19.5
/LORA_ANT: J_LORA1.1, U12.21
/LORA_ON: R52.1, U6.7, U19.13
/LORA_RXEN: U12.6, U32A.34
/LORA_TXEN: U12.7, U32A.54
/MCT3: R9.1, T1.18
/MCT4: R10.1, T1.15
/MDI_A_N: J_ETH.2, T1.22
/MDI_A_P: J_ETH.1, T1.23
/MDI_B_N: J_ETH.6, T1.19
/MDI_B_P: J_ETH.3, T1.20
/MDI_C_N: J_ETH.5, T1.16
/MDI_C_P: J_ETH.4, T1.17
/MDI_D_N: J_ETH.8, T1.13
/MDI_D_P: J_ETH.7, T1.14
/NVME1_CLKREQ_n: J_M2N1.52, R133.1
/NVME1_CLK_N: J_M2N1.53, U101.80
/NVME1_CLK_P: J_M2N1.55, U101.81
/NVME1_DEVSLP: J_M2N1.38, R135.1
/NVME1_RX_N: J_M2N1.41, U101.101
/NVME1_RX_P: J_M2N1.43, U101.100
/NVME1_TX_N: J_M2N1.47, U101.98
/NVME1_TX_P: J_M2N1.49, U101.97
/NVME1_nLED: J_M2N1.10, LED14.1
/NVME2_CLKREQ_n: J_M2N2.52, R233.1
/NVME2_CLK_N: J_M2N2.53, U201.80
/NVME2_CLK_P: J_M2N2.55, U201.81
/NVME2_DEVSLP: J_M2N2.38, R235.1
/NVME2_RX_N: J_M2N2.41, U201.101
/NVME2_RX_P: J_M2N2.43, U201.100
/NVME2_TX_N: J_M2N2.47, U201.98
/NVME2_TX_P: J_M2N2.49, U201.97
/NVME2_nLED: J_M2N2.10, LED24.1
/NVME3_CLKREQ_n: J_M2N3.52, R333.1
/NVME3_CLK_N: J_M2N3.53, U301.80
/NVME3_CLK_P: J_M2N3.55, U301.81
/NVME3_DEVSLP: J_M2N3.38, R335.1
/NVME3_RX_N: J_M2N3.41, U301.101
/NVME3_RX_P: J_M2N3.43, U301.100
/NVME3_TX_N: J_M2N3.47, U301.98
/NVME3_TX_P: J_M2N3.49, U301.97
/NVME3_nLED: J_M2N3.10, LED34.1
/PANEL_5V: F1.2, J_PANEL.1, J_PANEL.2
/PCIE1_CLKREQ_n: R129.1, U30B.102
/PCIE1_CLK_N: U30B.112, U101.73
/PCIE1_CLK_P: U30B.110, U101.74
/PCIE1_RCLK0_N: U101.83, U101.111
/PCIE1_RCLK0_P: U101.85, U101.110
/PCIE1_RST1_n: J_M2N1.50, U101.5
/PCIE1_RST2_n: J_M2C1.52, U101.6
/PCIE1_RX_N: U30B.118, U101.123
/PCIE1_RX_P: U30B.116, U101.124
/PCIE1_TX_N: U30B.124, U101.127
/PCIE1_TX_P: U30B.122, U101.128
/PCIE1_nRST: U30B.109, U101.10
/PCIE1_nWAKE: J_M2C1.55, J_M2N1.54, R132.1, U30B.104
/PCIE2_CLKREQ_n: R229.1, U31B.102
/PCIE2_CLK_N: U31B.112, U201.73
/PCIE2_CLK_P: U31B.110, U201.74
/PCIE2_RCLK0_N: U201.83, U201.111
/PCIE2_RCLK0_P: U201.85, U201.110
/PCIE2_RST1_n: J_M2N2.50, U201.5
/PCIE2_RST2_n: J_M2C2.50, U201.6
/PCIE2_RX_N: U31B.118, U201.123
/PCIE2_RX_P: U31B.116, U201.124
/PCIE2_TX_N: U31B.124, U201.127
/PCIE2_TX_P: U31B.122, U201.128
/PCIE2_nRST: U31B.109, U201.10
/PCIE2_nWAKE: J_M2C2.54, J_M2N2.54, R232.1, U31B.104
/PCIE3_CLKREQ_n: R329.1, U32B.102
/PCIE3_CLK_N: U32B.112, U301.73
/PCIE3_CLK_P: U32B.110, U301.74
/PCIE3_RCLK0_N: U301.83, U301.111
/PCIE3_RCLK0_P: U301.85, U301.110
/PCIE3_RST1_n: J_M2N3.50, U301.5
/PCIE3_RST2_n: J_M2C3.50, U301.6
/PCIE3_RX_N: U32B.118, U301.123
/PCIE3_RX_P: U32B.116, U301.124
/PCIE3_TX_N: U32B.124, U301.127
/PCIE3_TX_P: U32B.122, U301.128
/PCIE3_nRST: U32B.109, U301.10
/PCIE3_nWAKE: J_M2C3.54, J_M2N3.54, R332.1, U32B.104
/PCIE_PWR_EN1: R106.1, U30B.106, U103.3
/PCIE_PWR_EN2: R206.1, U31B.106, U203.3
/PCIE_PWR_EN3: R306.1, U32B.106, U303.3
/PI_KILL: J_AB1.2, J_PANEL.25, Q103.3, Q203.3, Q303.3
/PI_KILL_CM1: Q103.2, R155.1, U30A.50
/PI_KILL_CM2: Q203.2, R255.1, U31A.50
/PI_KILL_CM3: Q303.2, R355.1, U32A.50
/PI_SHDN_REQ: J_AB1.1, J_PANEL.24, Q102.3, Q202.3, Q302.3
/PI_SHDN_REQ_CM1: Q102.2, R154.1, U30A.30
/PI_SHDN_REQ_CM2: Q202.2, R254.1, U31A.30
/PI_SHDN_REQ_CM3: Q302.2, R354.1, U32A.30
/POE_DRAIN: Q1.5, T1.21, TP13.1, U5.16
/POE_GATE: Q1.4, U5.17
/POE_P: R13.2, T1.24
/POE_RST_n: R11.1, U5.2
/POE_SEN: Q1.1, Q1.2, Q1.3, R12.1, U5.15
/Q1B: Q101.1, R149.2
/Q1C: Q101.3, R150.1
/Q2B: Q201.1, R249.2
/Q2C: Q201.3, R250.1
/Q3B: Q301.1, R349.2
/Q3C: Q301.3, R350.1
/QMX_DM: J_QMX.2, U35.3, U35.4, U202.25
/QMX_DP: J_QMX.3, U35.1, U35.6, U202.24
/RB_3V3: C59.1, C60.1, R40.2, U18.6
/RB_CTRL: J_RB9704.6, U6.20
/RB_DM: U18.5, U102.25
/RB_DP: U18.4, U102.24
/RB_EN: U19.8, U24.3
/RB_FLT: R44.1, U7.5, U24.6
/RB_IEN: J_RB9704.3, U6.19
/RB_RST: R40.1, U18.9
/RB_RXD: J_RB9704.14, U18.26
/RB_STATUS: J_RB9704.7, R41.1, U7.7
/RB_SW_EN: R51.1, U6.6, U19.10
/RB_TXD: J_RB9704.13, U18.25
/RB_XMTG: J_RB9704.8, R42.1, U7.8
/S1A_BOOT: C111.1, U103.1
/S1A_COMP: R105.1, U103.6
/S1A_COMPC: C117.1, R105.2
/S1A_FB: R102.2, R103.1, U103.5
/S1A_RT: R104.1, U103.4
/S1A_SW: C111.2, L101.1, U103.8
/S1B_BOOT: C118.1, U104.1
/S1B_COMP: R110.1, U104.6
/S1B_COMPC: C124.1, R110.2
/S1B_FB: R107.2, R108.1, U104.5
/S1B_RT: R109.1, U104.4
/S1B_SW: C118.2, L102.1, U104.8
/S1C_BST: C128.1, U105.6
/S1C_FB: R113.2, R114.1, U105.8
/S1C_SS: C129.1, U105.7
/S1C_SW: C128.2, L103.1, U105.5
/S1D_BST: C133.1, U106.6
/S1D_FB: R115.2, R116.1, U106.8
/S1D_SS: C134.1, U106.7
/S1D_SW: C133.2, L104.1, U106.5
/S1_EEPD: R127.1, U101.71
/S1_IREF: R117.1, U101.86
/S1_JTAGL: R128.1, U101.89, U101.92, U101.93, U101.94
/S1_PRSNT3: R121.1, U101.21
/S1_PST0: LED12.1, U101.67
/S1_PST1: LED13.1, U101.68
/S1_PWRSAV: R122.1, U101.28
/S1_REXT: R118.1, U101.116
/S1_SLOTCLK: R119.1, U101.33
/S1_SLOTIMP: R120.1, U101.45, U101.46
/S1_SMBCLK: R125.1, U101.26
/S1_SMBDAT: R126.1, U101.27
/S1_TEST1: R123.1, U101.9
/S1_TESTL: R124.1, U101.16, U101.17, U101.18, U101.22, U101.25, U101.51
/S2A_BOOT: C211.1, U203.1
/S2A_COMP: R205.1, U203.6
/S2A_COMPC: C217.1, R205.2
/S2A_FB: R202.2, R203.1, U203.5
/S2A_RT: R204.1, U203.4
/S2A_SW: C211.2, L201.1, U203.8
/S2B_BOOT: C218.1, U204.1
/S2B_COMP: R210.1, U204.6
/S2B_COMPC: C224.1, R210.2
/S2B_FB: R207.2, R208.1, U204.5
/S2B_RT: R209.1, U204.4
/S2B_SW: C218.2, L202.1, U204.8
/S2C_BST: C228.1, U205.6
/S2C_FB: R213.2, R214.1, U205.8
/S2C_SS: C229.1, U205.7
/S2C_SW: C228.2, L203.1, U205.5
/S2D_BST: C233.1, U206.6
/S2D_FB: R215.2, R216.1, U206.8
/S2D_SS: C234.1, U206.7
/S2D_SW: C233.2, L204.1, U206.5
/S2_EEPD: R227.1, U201.71
/S2_IREF: R217.1, U201.86
/S2_JTAGL: R228.1, U201.89, U201.92, U201.93, U201.94
/S2_PRSNT3: R221.1, U201.21
/S2_PST0: LED22.1, U201.67
/S2_PST1: LED23.1, U201.68
/S2_PWRSAV: R222.1, U201.28
/S2_REXT: R218.1, U201.116
/S2_SLOTCLK: R219.1, U201.33
/S2_SLOTIMP: R220.1, U201.45, U201.46
/S2_SMBCLK: R225.1, U201.26
/S2_SMBDAT: R226.1, U201.27
/S2_TEST1: R223.1, U201.9
/S2_TESTL: R224.1, U201.16, U201.17, U201.18, U201.22, U201.25, U201.51
/S3A_BOOT: C311.1, U303.1
/S3A_COMP: R305.1, U303.6
/S3A_COMPC: C317.1, R305.2
/S3A_FB: R302.2, R303.1, U303.5
/S3A_RT: R304.1, U303.4
/S3A_SW: C311.2, L301.1, U303.8
/S3B_BOOT: C318.1, U304.1
/S3B_COMP: R310.1, U304.6
/S3B_COMPC: C324.1, R310.2
/S3B_FB: R307.2, R308.1, U304.5
/S3B_RT: R309.1, U304.4
/S3B_SW: C318.2, L302.1, U304.8
/S3C_BST: C328.1, U305.6
/S3C_FB: R313.2, R314.1, U305.8
/S3C_SS: C329.1, U305.7
/S3C_SW: C328.2, L303.1, U305.5
/S3D_BST: C333.1, U306.6
/S3D_FB: R315.2, R316.1, U306.8
/S3D_SS: C334.1, U306.7
/S3D_SW: C333.2, L304.1, U306.5
/S3_EEPD: R327.1, U301.71
/S3_IREF: R317.1, U301.86
/S3_JTAGL: R328.1, U301.89, U301.92, U301.93, U301.94
/S3_PRSNT3: R321.1, U301.21
/S3_PST0: LED32.1, U301.67
/S3_PST1: LED33.1, U301.68
/S3_PWRSAV: R322.1, U301.28
/S3_REXT: R318.1, U301.116
/S3_SLOTCLK: R319.1, U301.33
/S3_SLOTIMP: R320.1, U301.45, U301.46
/S3_SMBCLK: R325.1, U301.26
/S3_SMBDAT: R326.1, U301.27
/S3_TEST1: R323.1, U301.9
/S3_TESTL: R324.1, U301.16, U301.17, U301.18, U301.22, U301.25, U301.51
/SCL: J_AB1.14, J_PANEL.5, R55.1, TP11.1, U1.101, U5.3, U6.22, U7.22, U8.6, U9.8, U10.1
/SCL_CM1: J_DBG1.5, U30A.56
/SCL_CM2: J_DBG2.5, U31A.56
/SCL_CM3: J_DBG3.5, U32A.56
/SDA: J_AB1.13, J_PANEL.4, R54.1, TP10.1, U1.98, U5.4, U5.5, U6.23, U7.23, U8.5, U9.7, U10.6
/SDA_CM1: J_DBG1.4, U30A.58
/SDA_CM2: J_DBG2.4, U31A.58
/SDA_CM3: J_DBG3.4, U32A.58
/SHORE_INHIBIT: J_AB1.24, J_PANEL.26
/SIM1_CLK: C288.1, J_M2C2.32, J_SIM1.3
/SIM1_IO: C287.1, J_M2C2.34, J_SIM1.7
/SIM1_RST: J_M2C2.30, J_SIM1.2
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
